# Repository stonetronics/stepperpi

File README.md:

# stepperpi
control of one stepper motor (NEMA17) and measurement by rotary encoder with a raspberry pi through a ethernet interface  

## pcb
The pcb folder contains a PCB that fits on to a regular raspberry pi (drawn in KiCAD 9.0). It holds two A4988 stepper motor drivers complete with JST connector for a NEMA17 motor and two JST connectors for endswitches, all following common pin layouts as they are used with 3D printers. Options for microstepping are set through a solder jumper.  
Each hardware pin connection of both the stepper driver and endswitches is connected to the raspberry pi through a solder jumper and can be enabled/disabled as needed.  
An additional DC/DC converter is present on the board. It steps down the input voltage to the 5V needed by the raspberry pi, eliminating the need for a seperate USB power supply. The connection to the DC/DC converter is optional and can be enabled through a jumper.  

## code
In the code directory, three subdirectories exist. One holds a jupyter notebook for the analysis and development of the stepping algorithm and the other one holds a c++ project for the control of the stepper motor on the raspberry pi through a socket interface. Another directory holds a client written in python which connects to the raspberry pi's socket and enables the user to send and receive string commands and messages. Please refer to the respective readme for further info.

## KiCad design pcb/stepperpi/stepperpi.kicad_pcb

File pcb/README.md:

# PCB external content

This pcb uses/adapts external library content:

## A4988 step motor driver
3D model:  
https://grabcad.com/library/driver-a4988-1

## Raspberry Pi
3D model:  
https://grabcad.com/library/raspberry-pi-4-model-b-1
Footprint:
https://github.com/devbisme/RPi_Hat_Template

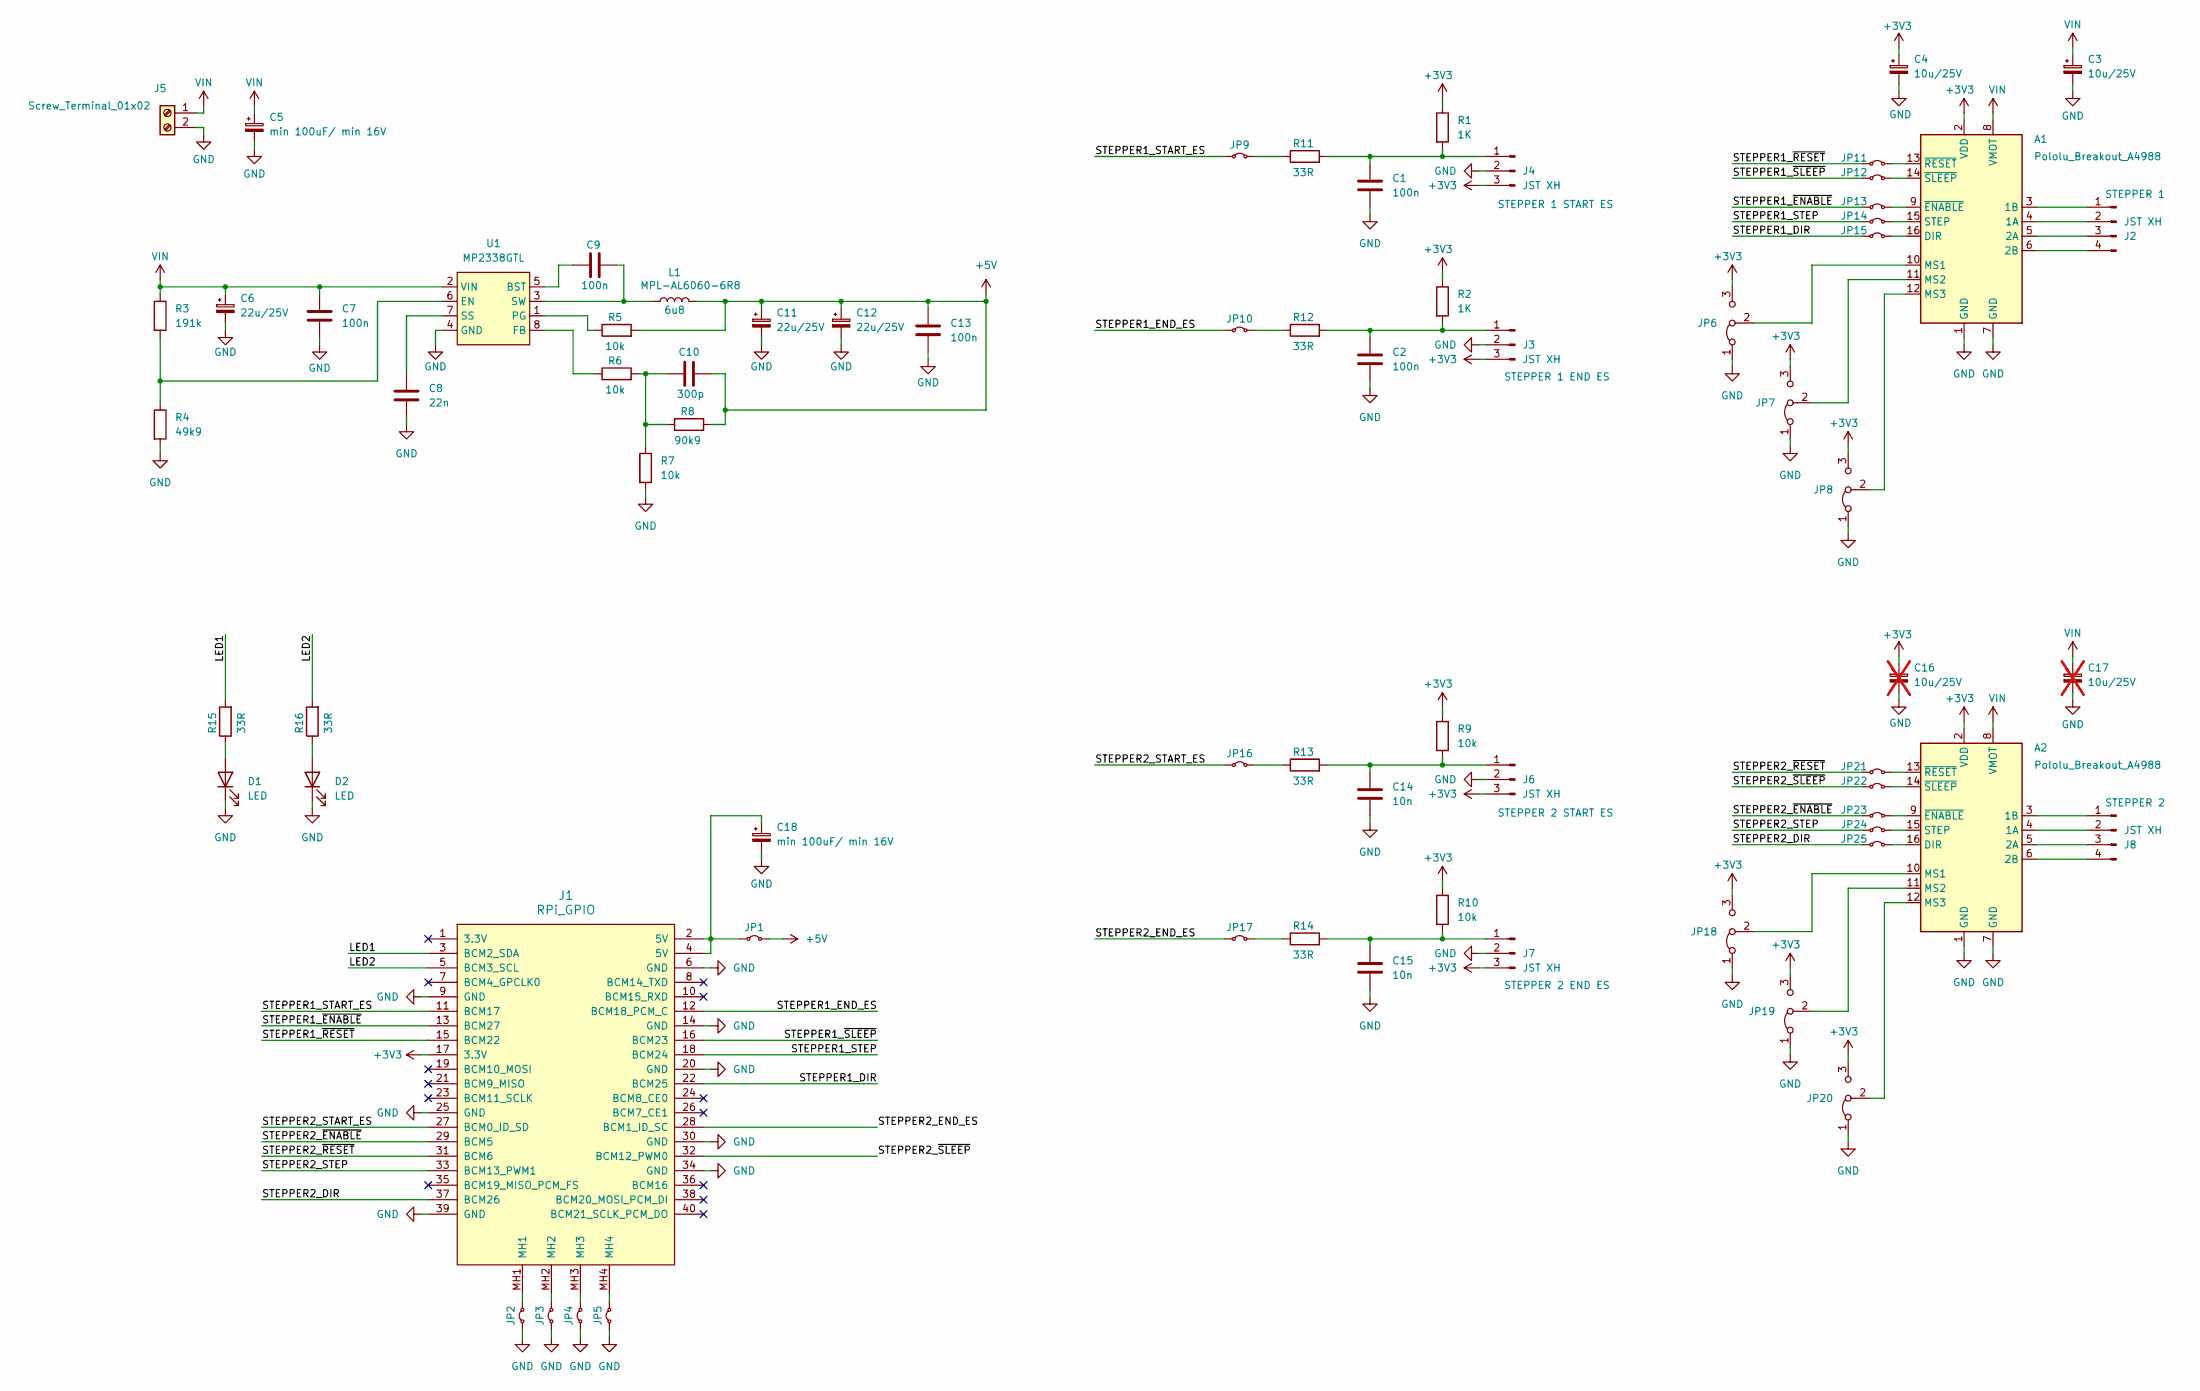
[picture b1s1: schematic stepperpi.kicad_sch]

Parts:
A1, A2: Pololu_Breakout_A4988; Pololu_Breakout-16_15.2x20.3mm
C1, C2, C7, C9, C13: 100n; C_0805_2012Metric
C3, C4: 10u/25V; CP_EIA-6032-28_Kemet-C_Pad2.25x2.35mm_HandSolder
C5, C18: min 100uF/ min 16V; CP_EIA-7343-31_Kemet-D_Pad2.25x2.55mm_HandSolder
C6, C11, C12: 22u/25V; CP_EIA-7132-28_AVX-C_Pad2.72x3.50mm_HandSolder
C8: 22n; C_0805_2012Metric
C10: 300p; C_0805_2012Metric
C14, C15: 10n; C_0805_2012Metric
C16, C17: 10u/25V; CP_EIA-6032-28_Kemet-C_Pad2.25x2.35mm_HandSolder; not fitted
D1, D2: LED; LED_0805_2012Metric_Pad1.15x1.40mm_HandSolder
J1: RPi_GPIO; RPI_Hat_B+ no display slot
J2, J8: JST XH; JST_XH_B4B-XH-A_1x04_P2.50mm_Vertical
J3, J4, J6, J7: JST XH; JST_XH_B3B-XH-A_1x03_P2.50mm_Vertical
J5: Screw_Terminal_01x02; TerminalBlock_bornier-2_P5.08mm
JP1, JP2, JP3, JP4, JP5, JP9, JP10, JP11, JP12, JP13, JP14, JP15, JP16, JP17, JP21, JP22, JP23, JP24, JP25: Jumper_2_Small_Bridged; SolderJumper-2_P1.3mm_Open_TrianglePad1.0x1.5mm
JP6, JP7, JP8, JP18, JP19, JP20: Jumper_3_Bridged12; SolderJumper-3_P2.0mm_Open_TrianglePad1.0x1.5mm_NumberLabels
L1: 6u8; L_MPL-AL6060-6R8; Part MPL-AL6060-6R8
R1, R2: 1K; R_0805_2012Metric
R3: 191k; R_0805_2012Metric
R4: 49k9; R_0805_2012Metric
R5, R6, R7, R9, R10: 10k; R_0805_2012Metric
R8: 90k9; R_0805_2012Metric
R11, R12, R13, R14, R15, R16: 33R; R_0805_2012Metric
U1: MP2338GTL; SOT-583-8

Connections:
+3V3: A1.2 (VDD), A2.2 (VDD), C4.1, C16.1, J1.17 (3.3V), J3.3, J4.3, J6.3, J7.3, JP6.3 (B), JP7.3 (B), JP8.3 (B), JP18.3 (B), JP19.3 (B), JP20.3 (B), R1.1, R2.1, R9.1, R10.1
+5V: C10.2, C11.1, C12.1, C13.1, JP1.1 (A), L1.2, R5.2, R8.2
/LED1: J1.3 (BCM2_SDA), R15.2
/LED2: J1.5 (BCM3_SCL), R16.2
/STEPPER1_DIR: J1.22 (BCM25), JP15.1 (A)
/STEPPER1_END_ES: J1.12 (BCM18_PCM_C), JP10.1 (A)
/STEPPER1_START_ES: J1.11 (BCM17), JP9.1 (A)
/STEPPER1_STEP: J1.18 (BCM24), JP14.1 (A)
/STEPPER1_~ENABLE: J1.13 (BCM27), JP13.1 (A)
/STEPPER1_~RESET: J1.15 (BCM22), JP11.1 (A)
/STEPPER1_~SLEEP: J1.16 (BCM23), JP12.1 (A)
/STEPPER2_DIR: J1.37 (BCM26), JP25.1 (A)
/STEPPER2_END_ES: J1.28 (BCM1_ID_SC), JP17.1 (A)
/STEPPER2_START_ES: J1.27 (BCM0_ID_SD), JP16.1 (A)
/STEPPER2_STEP: J1.33 (BCM13_PWM1), JP24.1 (A)
/STEPPER2_~ENABLE: J1.29 (BCM5), JP23.1 (A)
/STEPPER2_~RESET: J1.31 (BCM6), JP21.1 (A)
/STEPPER2_~SLEEP: J1.32 (BCM12_PWM0), JP22.1 (A)
GND: A1.1 (GND), A1.7 (GND), A2.1 (GND), A2.7 (GND), C1.2, C2.2, C3.2, C4.2, C5.2, C6.2, C7.2, C8.2, C11.2, C12.2, C13.2, C14.2, C15.2, C16.2, C17.2, C18.2, D1.1 (K), D2.1 (K), J1.6 (GND), J1.9 (GND), J1.14 (GND), J1.20 (GND), J1.25 (GND), J1.30 (GND), J1.34 (GND), J1.39 (GND), J3.2, J4.2, J5.2, J6.2, J7.2, JP2.1 (A), JP3.1 (A), JP4.1 (A), JP5.1 (A), JP6.1 (A), JP7.1 (A), JP8.1 (A), JP18.1 (A), JP19.1 (A), JP20.1 (A), R4.2, R7.2, U1.4 (GND)
unnamed: A1.4 (1A), J2.2
unnamed: A1.3 (1B), J2.1
unnamed: A1.5 (2A), J2.3
unnamed: A1.6 (2B), J2.4
unnamed: A1.16 (DIR), JP15.2 (B)
unnamed: A1.10 (MS1), JP6.2 (C)
unnamed: A1.11 (MS2), JP7.2 (C)
unnamed: A1.12 (MS3), JP8.2 (C)
unnamed: A1.15 (STEP), JP14.2 (B)
unnamed: A1.9 (~ENABLE), JP13.2 (B)
unnamed: A1.13 (~RESET), JP11.2 (B)
unnamed: A1.14 (~SLEEP), JP12.2 (B)
unnamed: A2.4 (1A), J8.2
unnamed: A2.3 (1B), J8.1
unnamed: A2.5 (2A), J8.3
unnamed: A2.6 (2B), J8.4
unnamed: A2.16 (DIR), JP25.2 (B)
unnamed: A2.10 (MS1), JP18.2 (C)
unnamed: A2.11 (MS2), JP19.2 (C)
unnamed: A2.12 (MS3), JP20.2 (C)
unnamed: A2.15 (STEP), JP24.2 (B)
unnamed: A2.9 (~ENABLE), JP23.2 (B)
unnamed: A2.13 (~RESET), JP21.2 (B)
unnamed: A2.14 (~SLEEP), JP22.2 (B)
unnamed: C10.1, R6.2, R7.1, R8.1
unnamed: D1.2 (A), R15.1
unnamed: D2.2 (A), R16.1
unnamed: C2.1, J3.1, R2.2, R12.2
unnamed: C1.1, J4.1, R1.2, R11.2
unnamed: C14.1, J6.1, R9.2, R13.2
unnamed: C15.1, J7.1, R10.2, R14.2
unnamed: C18.1, J1.2 (5V), J1.4 (5V), JP1.2 (B)
unnamed: J1.MH1, JP2.2 (B)
unnamed: J1.MH2, JP3.2 (B)
unnamed: J1.MH3, JP4.2 (B)
unnamed: J1.MH4, JP5.2 (B)
unnamed: JP9.2 (B), R11.1
unnamed: JP10.2 (B), R12.1
unnamed: JP16.2 (B), R13.1
unnamed: JP17.2 (B), R14.1
unnamed: C9.1, U1.5 (BST)
unnamed: R3.2, R4.1, U1.6 (EN)
unnamed: R6.1, U1.8 (FB)
unnamed: R5.1, U1.1 (PG)
unnamed: C8.1, U1.7 (SS)
unnamed: C9.2, L1.1, U1.3 (SW)
VIN: A1.8 (VMOT), A2.8 (VMOT), C3.1, C5.1, C6.1, C7.1, C17.1, J5.1, R3.1, U1.2 (VIN)

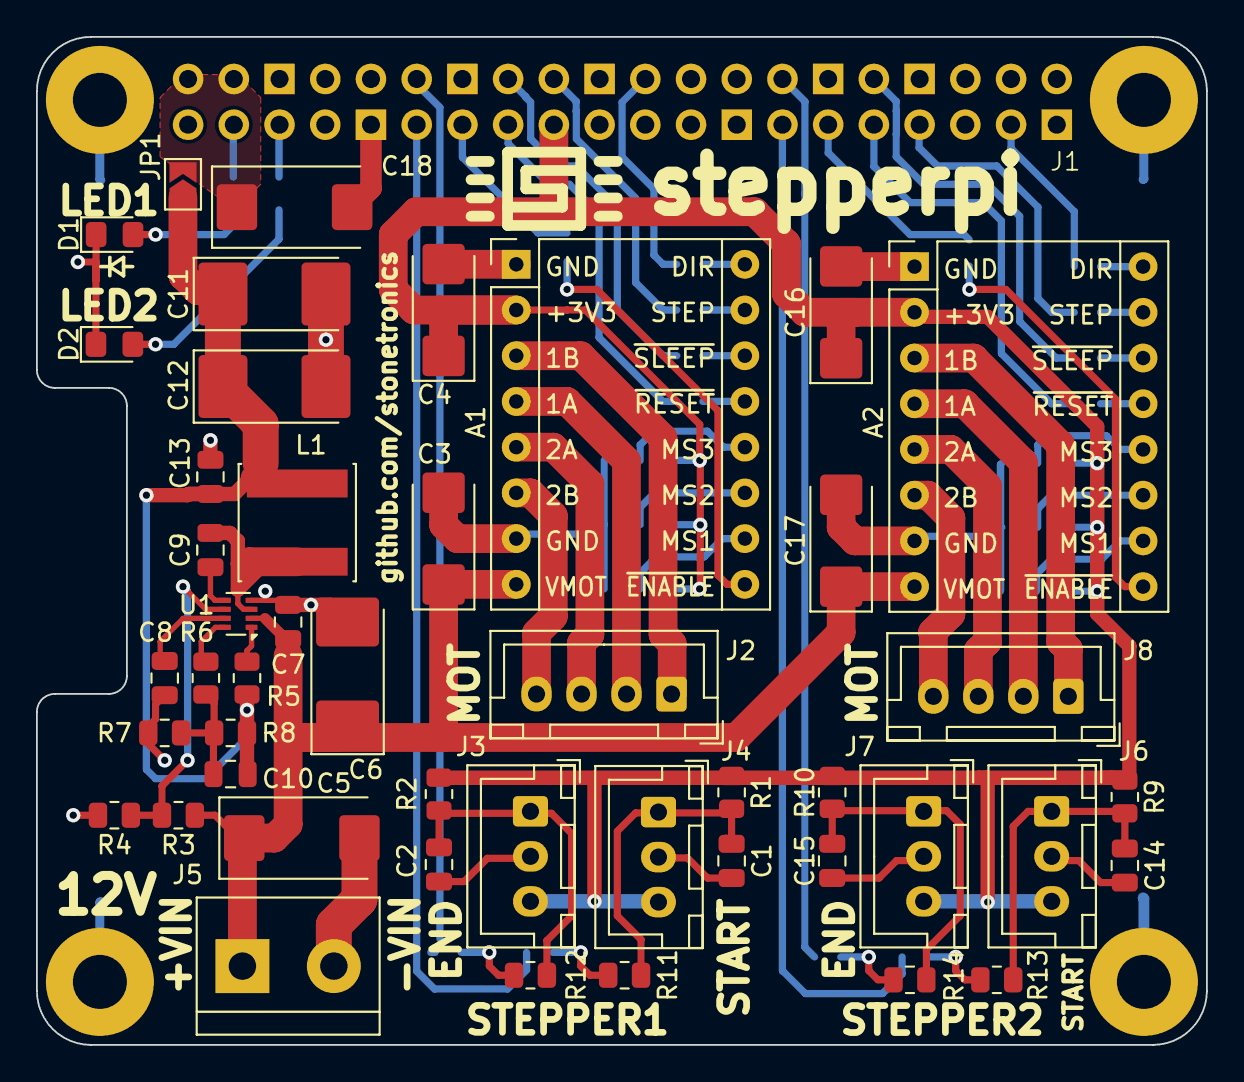
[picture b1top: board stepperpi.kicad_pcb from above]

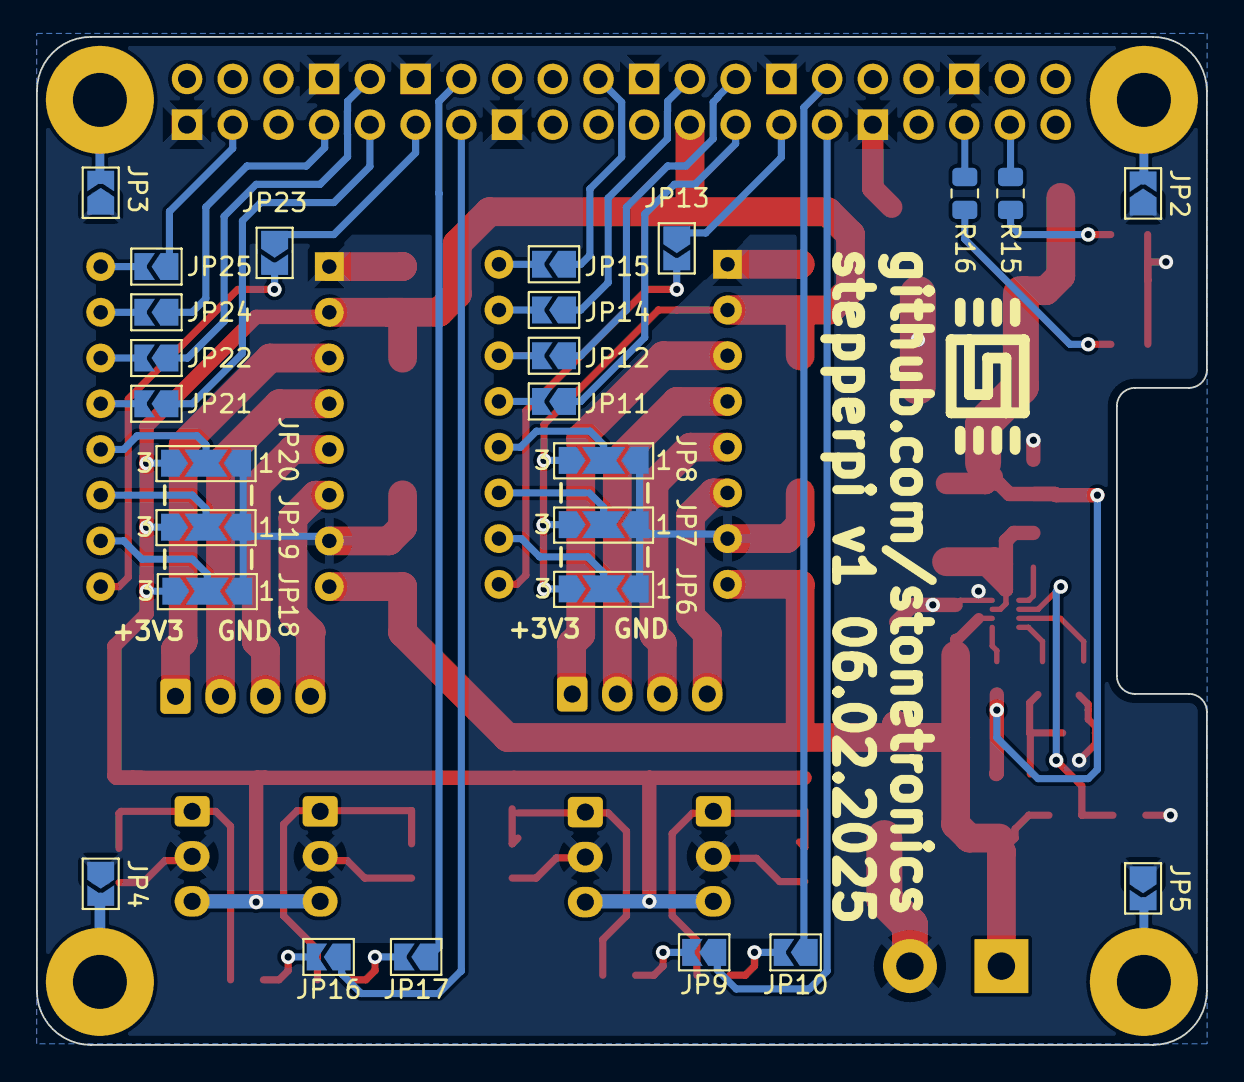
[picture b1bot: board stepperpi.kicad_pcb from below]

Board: 2 copper layers, 65.0 x 56.0 mm, 73 parts (26 on the bottom side), 66 nets.

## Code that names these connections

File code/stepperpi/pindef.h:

#define NO_STEPPERS             1

// GPIO connections from the schematic
#define STEPPER1_DIR        25
#define STEPPER1_STEP       24
#define STEPPER1_nSLEEP     23
#define STEPPER1_nRESET     22
#define STEPPER1_nENABLE    27
#define STEPPER1_START_ES   17
#define STEPPER1_END_ES     18

#define STEPPER2_DIR        26
#define STEPPER2_STEP       13
#define STEPPER2_nSLEEP     12
#define STEPPER2_nRESET     6
#define STEPPER2_nENABLE    5
#define STEPPER2_START_ES   0
#define STEPPER2_END_ES     1

//define GPIO connections which are used in the program
#define A4988_DIR       STEPPER1_DIR
#define A4988_STEP      STEPPER1_STEP
#define A4988_nSLEEP    STEPPER1_nSLEEP
#define A4988_nRESET    STEPPER1_nRESET
//#define SET_MICROSTEPS_PINS
#ifdef SET_MICROSTEPS_PINS
 #define A4988_MS3       11
 #define A4988_MS2       0
 #define A4988_MS1       5
#endif
#define A4988_nENABLE   STEPPER1_nENABLE
#define ENDSTOP_START   STEPPER1_START_ES
#define ENDSTOP_STOP    STEPPER1_END_ES


//set GPIO connections for LEDs
#define LED1_PIN    2
#define LED2_PIN    3


//set GPIO connections for rotary encoder
#define LIGHTBARRIER_A      STEPPER2_START_ES
#define LIGHTBARRIER_B      STEPPER2_END_ES


//set GPIO connections for manual mode panel
#define MANUAL_ENABLE   STEPPER2_STEP
#define MANUAL_LEFT     STEPPER2_nSLEEP
#define MANUAL_RIGHT    STEPPER2_nRESET
#define MANUAL_LED      STEPPER2_DIR

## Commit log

2025-04-23 initial commit for the pcb
2025-04-23 add links to content provided externally
2025-04-29 code's initial commit
2025-05-07 restructure code directory, add readme files and analysis of step rate ramp/profile in a jupyter notebook
2025-05-07 Add python client script and .gitignore files
2025-05-07 fix client script ctrl c issues
2025-05-07 clean client script a little bit more
2025-05-07 add acceleration to the movement
2025-05-07 .gitignore the executable
2025-05-12 add encoder on second stepper endstop inputs, add makefile option to install the program as service
2025-05-12 add option in client script to select host and port
2025-05-13 synchronize pin definition in code with pin definition in schematic
2025-05-14 add manual control through enable/left/right buttons
